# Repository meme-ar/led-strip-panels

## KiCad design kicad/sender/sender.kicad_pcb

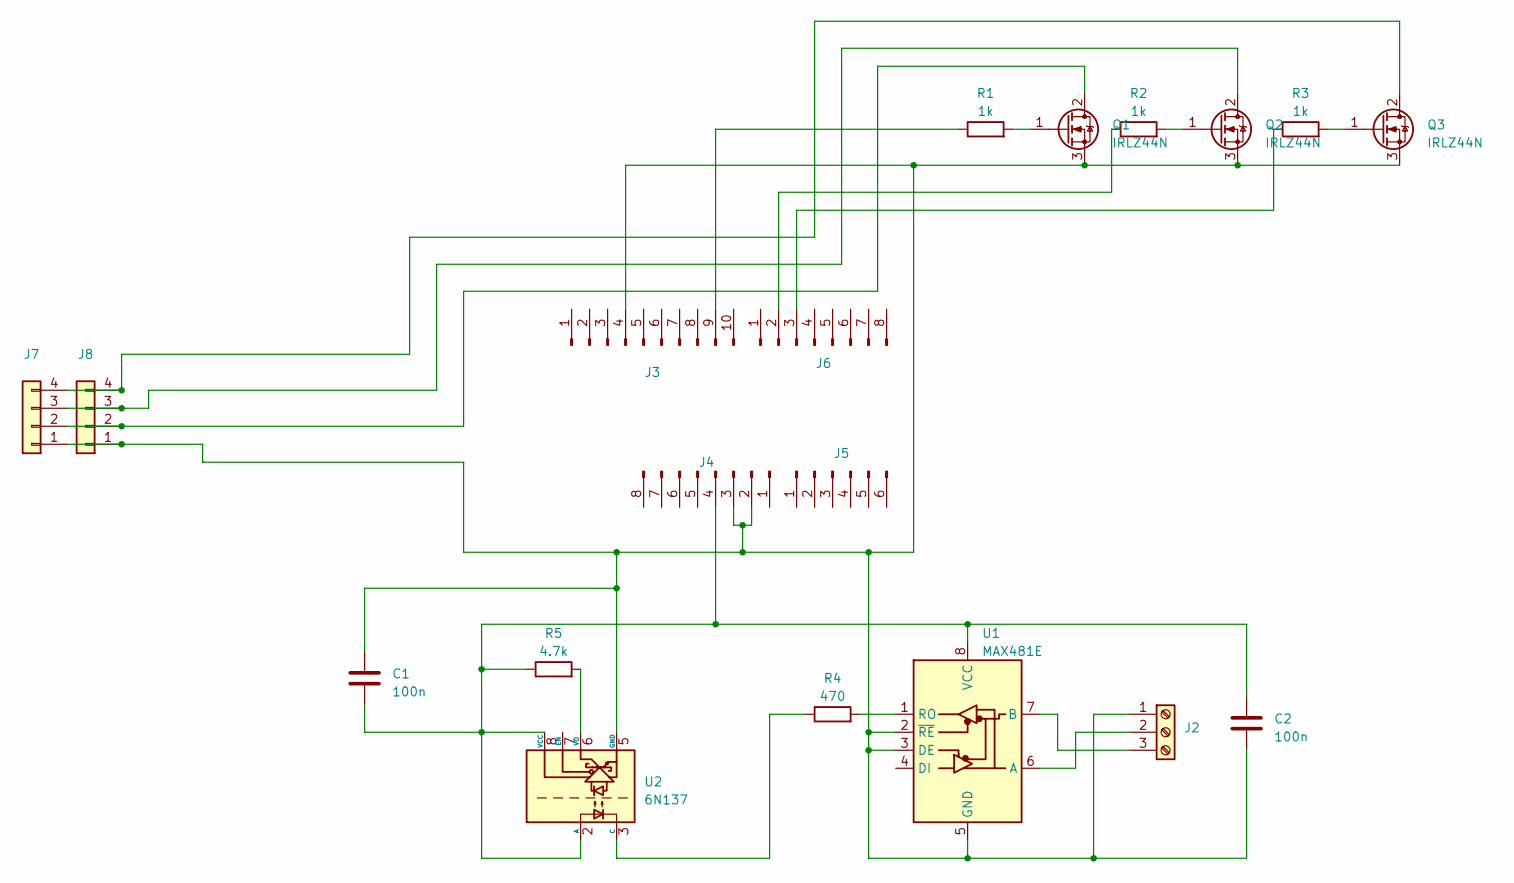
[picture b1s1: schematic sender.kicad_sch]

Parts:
C1, C2: 100n; C_Rect_L7.2mm_W2.5mm_P5.00mm_FKS2_FKP2_MKS2_MKP2
J2: Screw_Terminal_01x03; TerminalBlock_Phoenix_MKDS-1,5-3-5.08_1x03_P5.08mm_Horizont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
J3: Conn_01x10_Pin; PinHeader_1x10_P2.54mm_Vertical
J4, J6: Conn_01x08_Pin; PinHeader_1x08_P2.54mm_Vertical
J5: Conn_01x06_Pin; PinHeader_1x06_P2.54mm_Vertical
J7, J8: Conn_01x04; PinHeader_1x04_P2.00mm_Vertical
Q1, Q2, Q3: IRLZ44N; TO-220-3_Vertical
R1, R2, R3: 1k; R_Axial_DIN0207_L6.3mm_D2.5mm_P10.16mm_Horizontal
R4: 470; R_Axial_DIN0207_L6.3mm_D2.5mm_P10.16mm_Horizontal
R5: 4.7k; R_Axial_DIN0207_L6.3mm_D2.5mm_P10.16mm_Horizontal
U1: MAX481E; DIP-8_W7.62mm_Socket_LongPads
U2: 6N137; DIP-8_W7.62mm_Socket_LongPads

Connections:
unnamed: C1.1, C2.2, J2.1, J3.4, J4.2, J4.3, J7.1, J8.1, Q1.3 (S), Q2.3 (S), Q3.3 (S), U1.2 (~RE), U1.3 (DE), U1.5 (GND), U2.5 (GND)
unnamed: J2.2, U1.6 (A)
unnamed: J2.3, U1.7 (B)
unnamed: J3.9, R1.1
unnamed: C1.2, C2.1, J4.4, R5.1, U1.8 (VCC), U2.2 (A), U2.8 (VCC)
unnamed: J6.2, R2.1
unnamed: J6.3, R3.1
unnamed: J7.2, J8.2, Q1.2 (D)
unnamed: J7.3, J8.3, Q2.2 (D)
unnamed: J7.4, J8.4, Q3.2 (D)
unnamed: Q1.1 (G), R1.2
unnamed: Q2.1 (G), R2.2
unnamed: Q3.1 (G), R3.2
unnamed: R4.2, U1.1 (RO)
unnamed: R4.1, U2.3 (C)
unnamed: R5.2, U2.6 (VO)

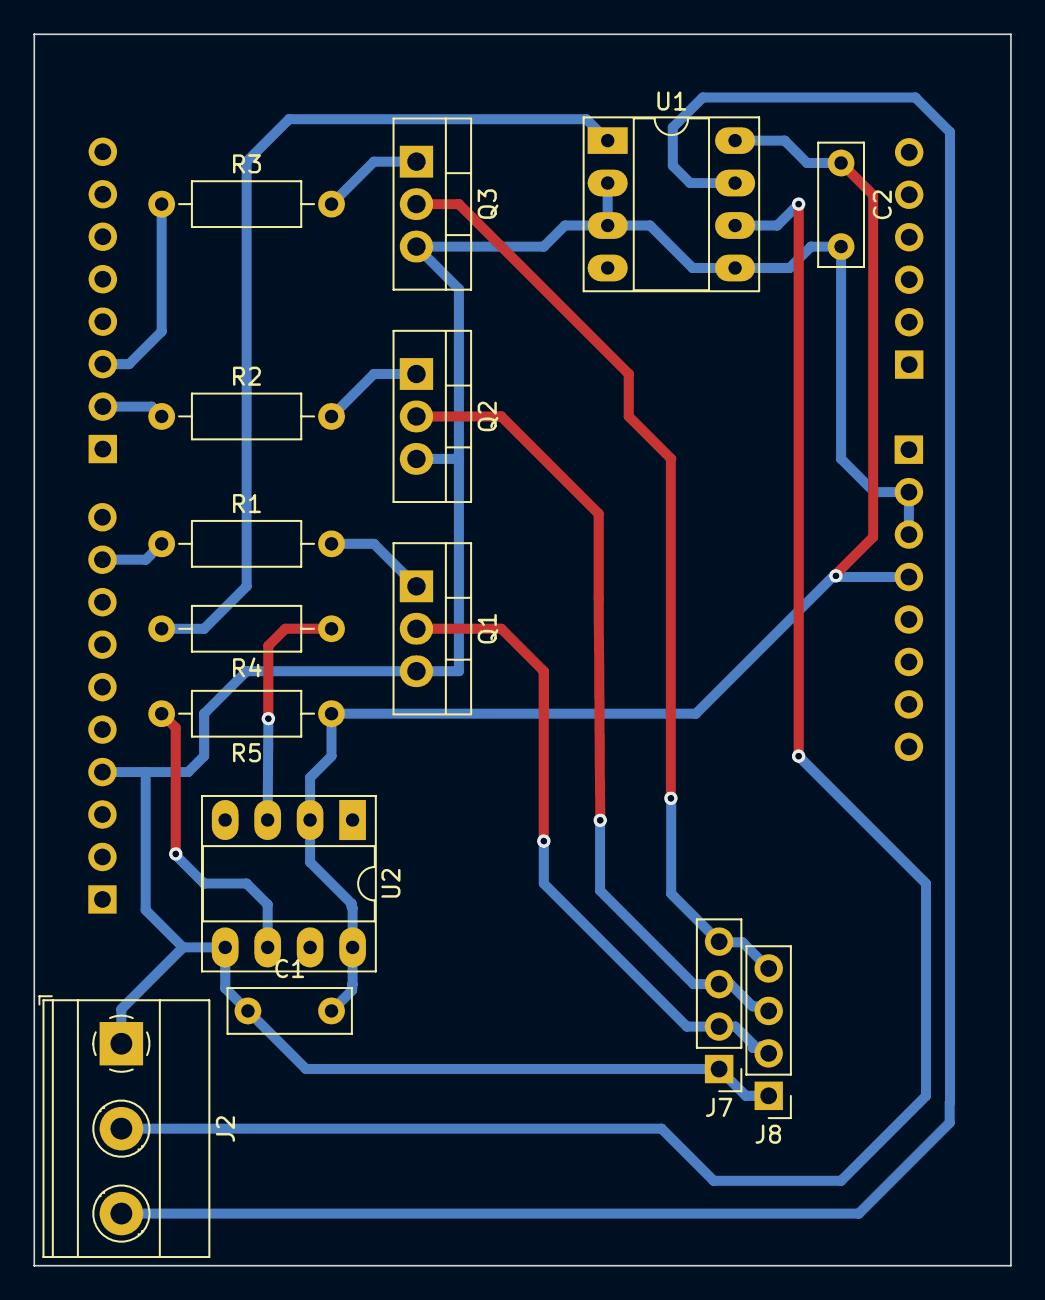
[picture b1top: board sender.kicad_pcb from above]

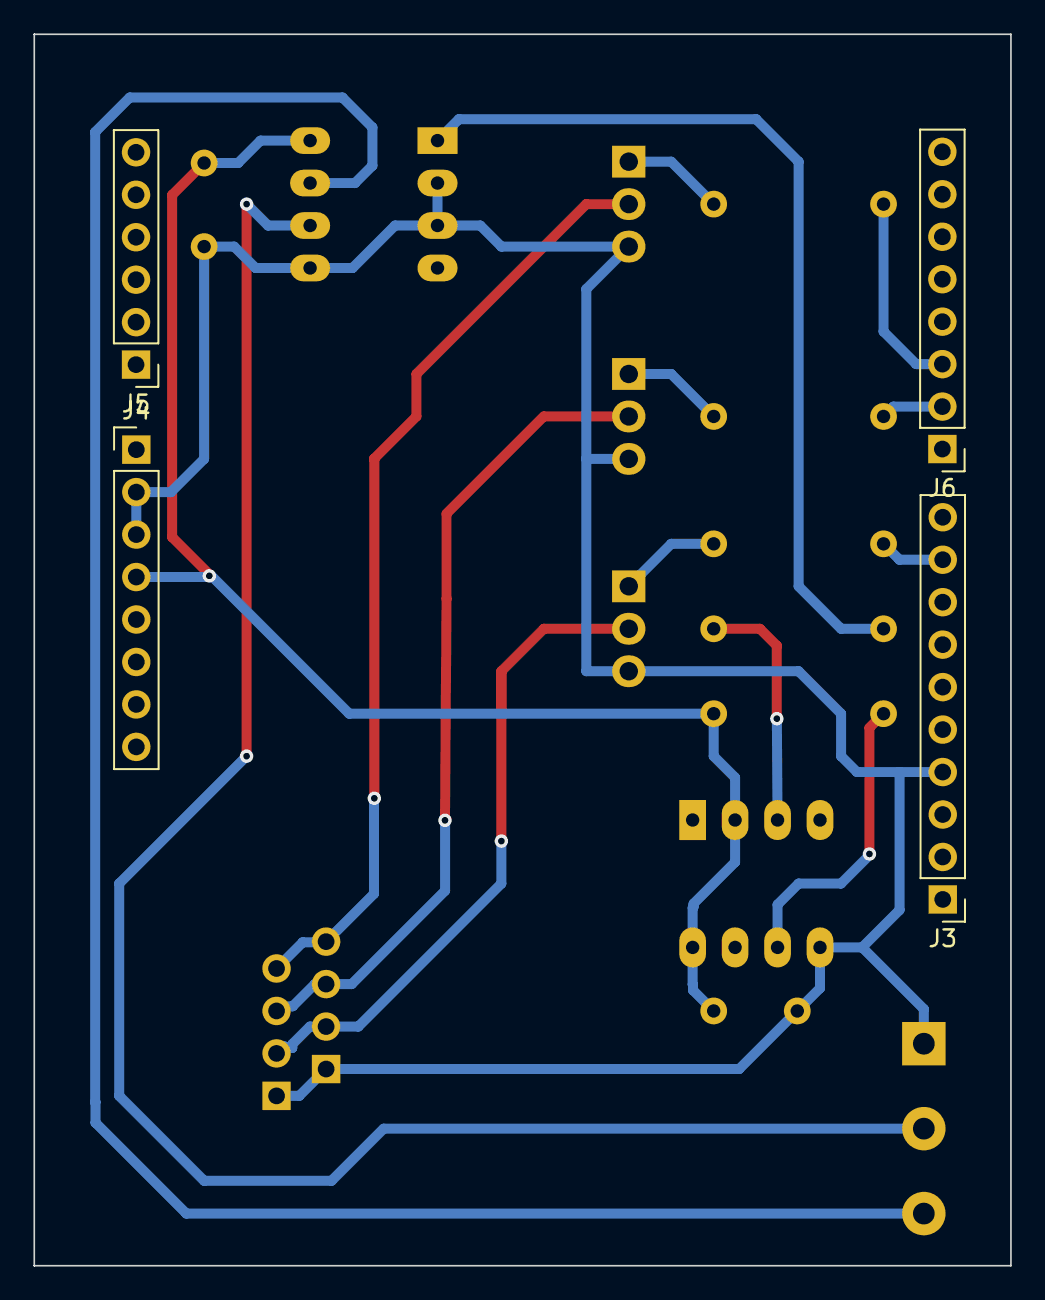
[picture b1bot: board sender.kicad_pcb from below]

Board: 2 copper layers, 58.4 x 73.7 mm, 19 parts (4 on the bottom side), 16 nets.

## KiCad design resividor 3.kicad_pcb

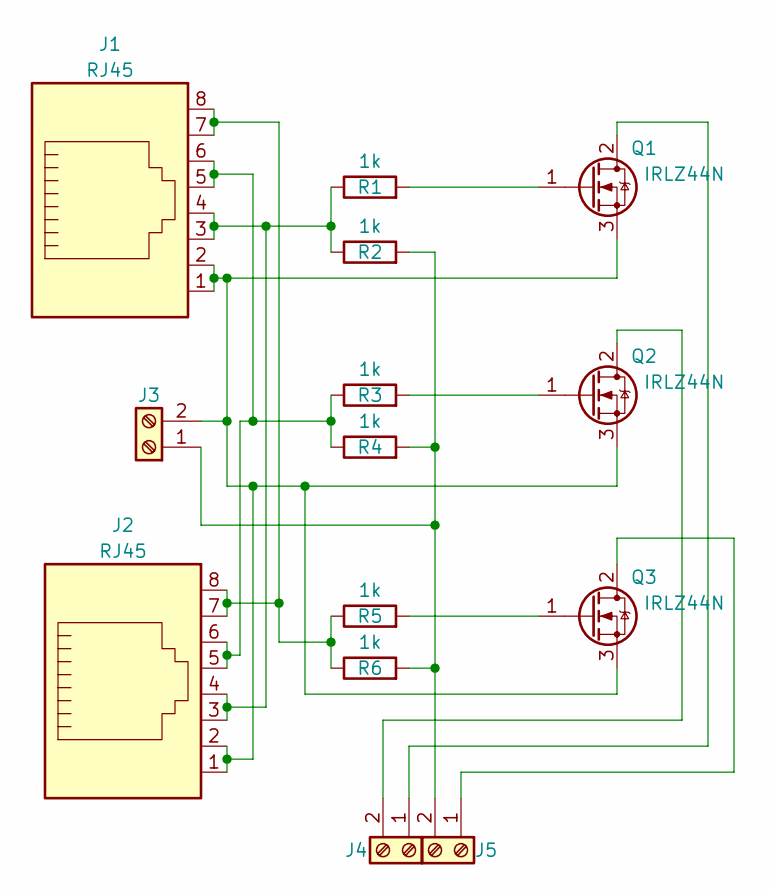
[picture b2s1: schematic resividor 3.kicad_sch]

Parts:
J1, J2: RJ45; RJ45_Amphenol_54602-x08_Horizontal
J3, J4, J5: Screw_Terminal_01x02; TerminalBlock_Phoenix_MKDS-1,5-2-5.08_1x02_P5.08mm_Horizont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
Q1, Q2, Q3: IRLZ44N; TO-220-3_Vertical
R1, R2, R3, R4, R5, R6: 1k; R_Axial_DIN0207_L6.3mm_D2.5mm_P10.16mm_Horizontal

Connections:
unnamed: J1.3, J1.4, J2.3, J2.4, R1.1, R2.1
unnamed: J1.5, J1.6, J2.5, J2.6, R3.1, R4.1
unnamed: J1.7, J1.8, J2.7, J2.8, R5.1, R6.1
unnamed: J3.1, J5.2, R2.2, R4.2, R6.2
unnamed: J1.1, J1.2, J2.1, J2.2, J3.2, Q1.3 (S), Q2.3 (S), Q3.3 (S)
unnamed: J4.1, Q1.2 (D)
unnamed: J4.2, Q2.2 (D)
unnamed: J5.1, Q3.2 (D)
unnamed: Q1.1 (G), R1.2
unnamed: Q2.1 (G), R3.2
unnamed: Q3.1 (G), R5.2

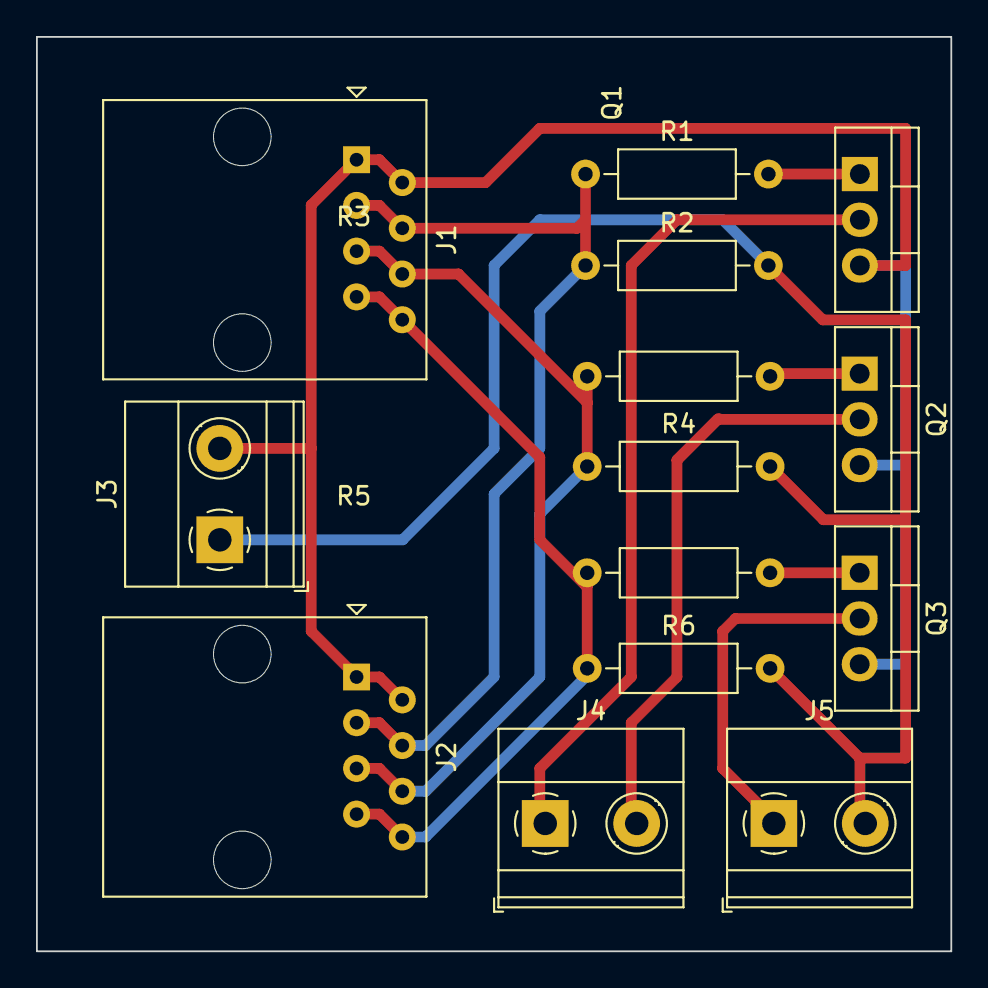
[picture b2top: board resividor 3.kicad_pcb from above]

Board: 2 copper layers, 50.8 x 50.8 mm, 14 parts (0 on the bottom side), 11 nets.

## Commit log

2023-02-07 sender upd
2023-02-15 Create kek
2023-02-15 Create e
